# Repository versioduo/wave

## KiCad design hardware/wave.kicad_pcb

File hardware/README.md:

# wave
🔊 MIDI Wave Synthesizer with Class-D Amplifier 

## Schematic
[PDF](wave.pdf)

## Bill Of Materials
[Interactive BOM](https://html-preview.github.io/?url=https://github.com/versioduo/wave/main/hardware/wave-bom.html)

# Copying
Anyone can use this public domain work without having to seek authorisation, no one can ever own it.

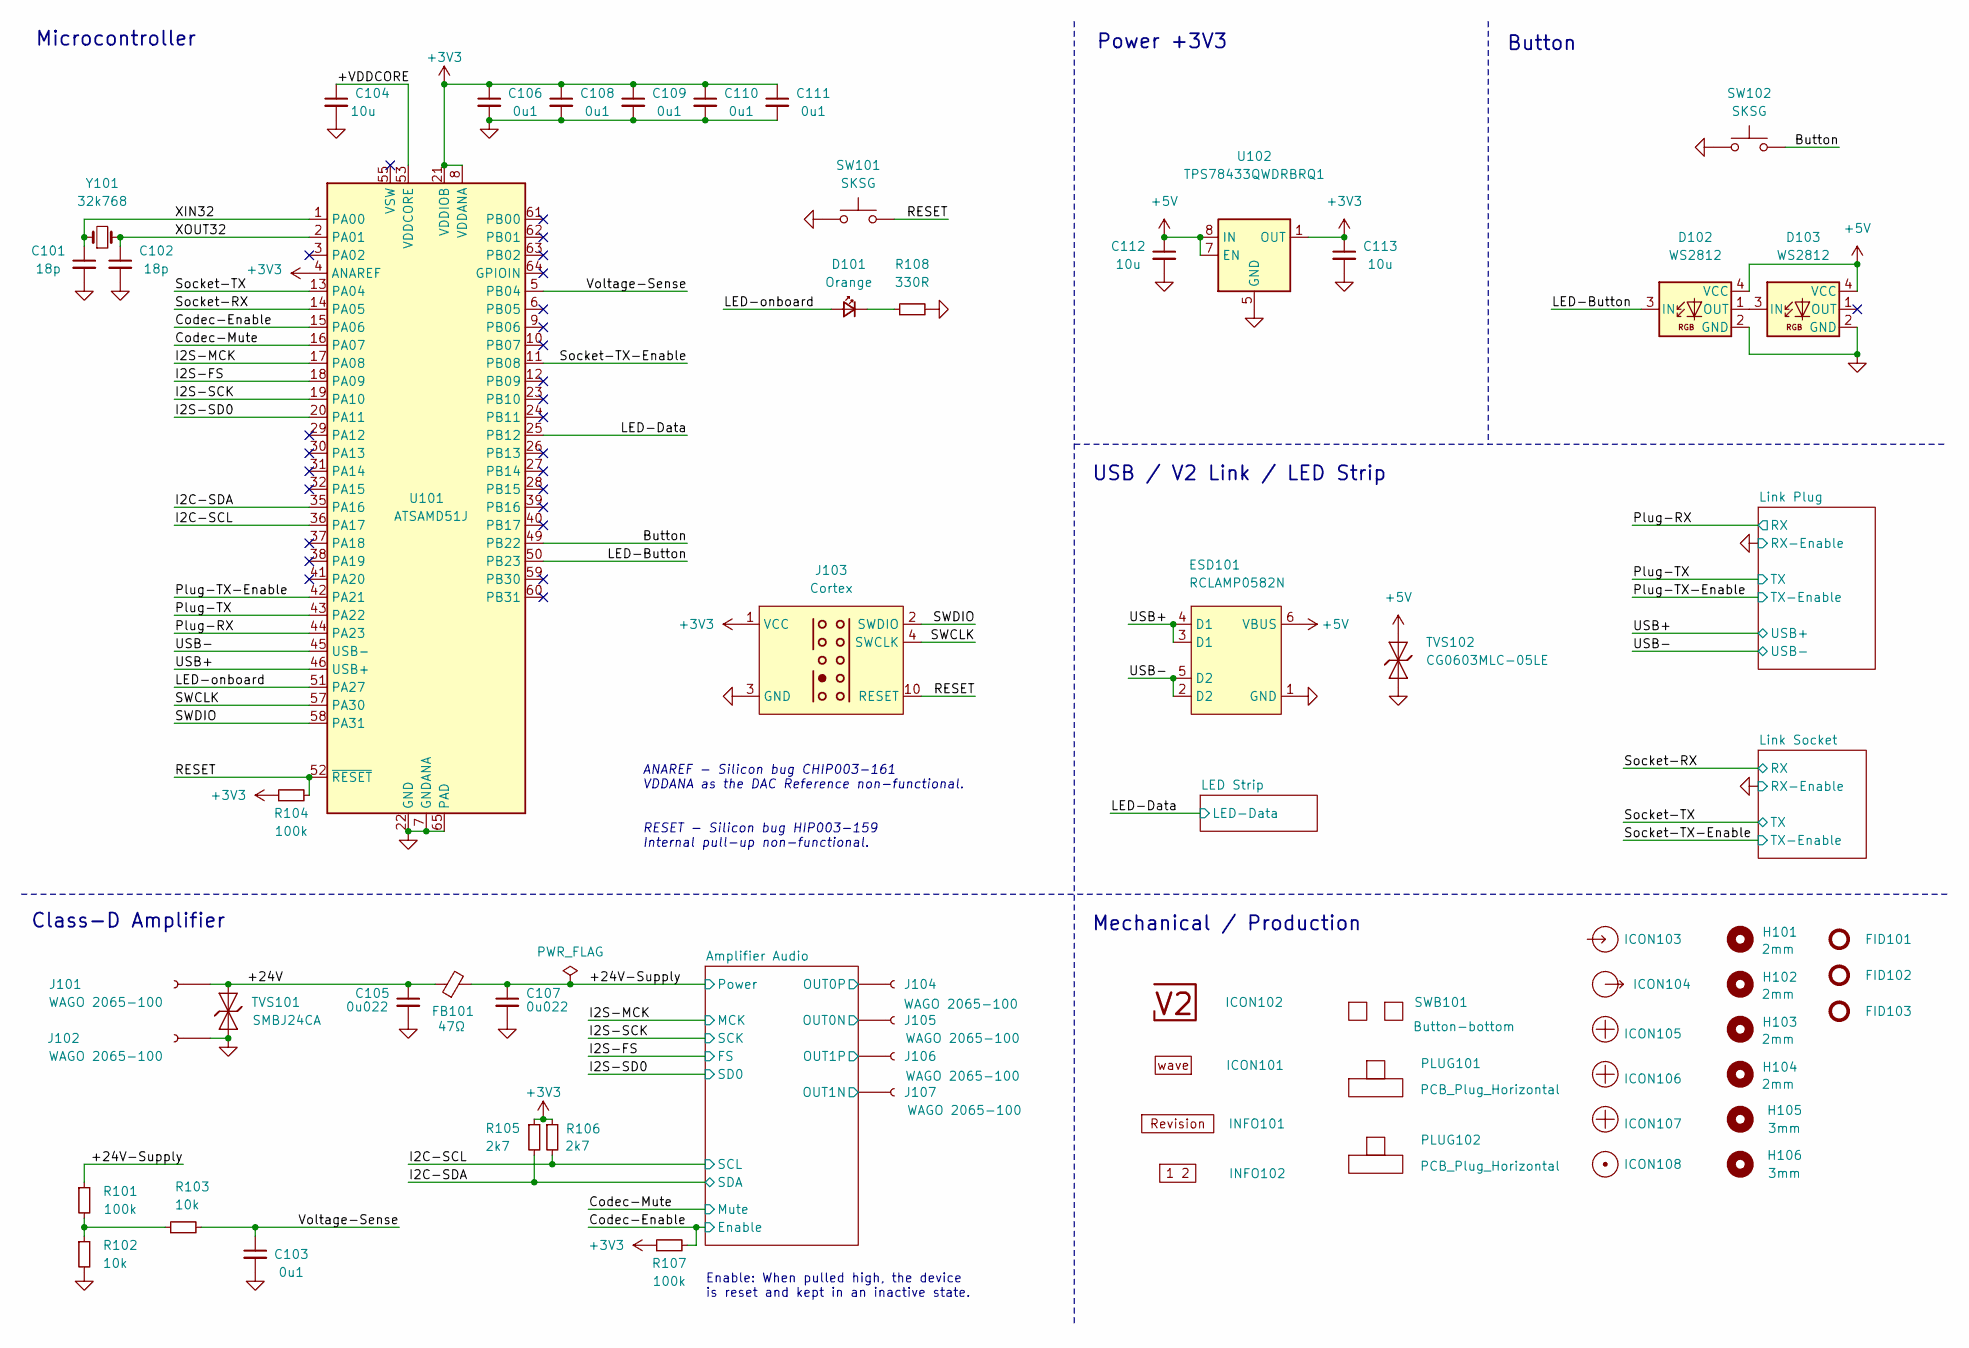
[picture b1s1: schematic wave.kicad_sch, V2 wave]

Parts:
C101, C102: 18p; C_1608; Rating 50V; Mouser 810-CGA3E2C0G1H180J
C103, C106, C108, C109, C110, C111: 0u1; C_1608; Rating 50V; Mouser 810-CGA3E2X7R1H104MA
C104: 10u; C_1608; Rating 10V; Mouser 810-C1608X6S1A106M
C105, C107: 0u022; C_1608; Rating 50V; Mouser 603-CC603KPX7R9BB223
C112, C113: 10u; C_2012; Rating 25V; Mouser 810-C2012X5R1E106K
D101: Orange; LED_1608; Rating 605nm; Mouser 755-SML-D12D1WT86
D102, D103: WS2812; WS2812-2020; Rating 15mA; LCSC C965555
ESD101: RCLAMP0582N; SLP1210N6; Rating 20kV; Mouser 947-RCLAMP0582N.TCT
FB101: 47Ω; L_3.1x5.1; Rating 5A; Mouser 623-2743019447LF
FID101, FID102, FID103: Fiducial_Paste; Fiducial_0.5mm_Mask1mm_Paste
H101, H102, H103, H104: 2mm; MountingHole_2mm
H105, H106: 3mm; MountingHole_3mm
ICON101: Board_wave; Board_wave_Small
ICON102: V2-logo; Logo_Small
ICON103: Arrow_In
ICON104: Arrow_Out
ICON105, ICON106, ICON107: Plus; Plus_Small
ICON108: Dot; Dot_Small
INFO101: Revision
INFO102: Layer_Numbers-4
J101, J102, J104, J105, J106, J107: WAGO 2065-100; 2065-100; Rating 9A
J103: Cortex
PLUG101, PLUG102: PCB_Plug_Horizontal
R101, R104, R107: 100k; R_1608; Rating 100mW; Mouser 71-CRCW0603100KFKEAC
R102, R103: 10k; R_1608; Rating 100mW; Mouser 71-CRCW060310K0FKEAC
R105, R106: 2k7; R_1608; Rating 100mW; Mouser 71-CRCW06032K70FKEAC
R108: 330R; R_1608; Rating 100mW; Mouser 71-CRCW0603330RFKEAC
SW101, SW102: SKSG; Rating 1.6N; Mouser 688-SKSGACE010
SWB101: Button-bottom; PCB_Button-bottom
TVS101: SMBJ24CA; D_SMB; Rating 24V; Mouser 652-SMBJ24CA-Q
TVS102: CG0603MLC-05LE; D_1608; Rating 5V; Mouser 652-CG0603MLC-05LE
U101: ATSAMD51J; QFN-64-1EP_9x9mm_P0.5mm_EP4.8x4.8mm_ThermalVias; Rating Cortex-M4F; Mouser 556-ATSAMD51J19AMU
U102: TPS78433QWDRBRQ1; VSON-8-1_3x3mm_P0.65_EP1.65x2.4mm; Rating 300mA; Mouser 595-TPS78433QWDRBRQ1
Y101: 32k768; Crystal_SMD_3215-2Pin_3.2x1.5mm; Rating 10ppm; Mouser 815-ABS0716632.768KT

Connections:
+3V3: C106.1, C108.1, C109.1, C110.1, C111.1, C113.1, J103.1 (VCC), R104.1, R105.1, R106.1, R107.1, U101.4 (ANAREF), U101.8 (VDDANA), U101.21 (VDDIOB), U101.34 (VDDIO), U101.48 (VDDIO), U101.56 (VDDIO), U102.1 (OUT); also elsewhere on the board
+5V: C112.1, D102.4 (VCC), D103.4 (VCC), ESD101.6 (VBUS), TVS102.2 (A), U102.7 (EN), U102.8 (IN); also elsewhere on the board
/+24V: C105.1, FB101.1, J101.1, TVS101.2 (A)
/+24V-Supply: C107.1, FB101.2, R101.1; also elsewhere on the board
/+VDDCORE: C104.1, U101.53 (VDDCORE)
/Amplifier Audio/OUT0N: J105.1; also elsewhere on the board
/Amplifier Audio/OUT0P: J104.1; also elsewhere on the board
/Amplifier Audio/OUT1N: J107.1; also elsewhere on the board
/Amplifier Audio/OUT1P: J106.1; also elsewhere on the board
/Button: SW102.2, U101.49 (PB22)
/Codec-Enable: R107.2, U101.15 (PA06); also elsewhere on the board
/Codec-Mute: U101.16 (PA07); also elsewhere on the board
/I2C-SCL: R106.2, U101.36 (PA17); also elsewhere on the board
/I2C-SDA: R105.2, U101.35 (PA16); also elsewhere on the board
/I2S-FS: U101.18 (PA09); also elsewhere on the board
/I2S-MCK: U101.17 (PA08); also elsewhere on the board
/I2S-SCK: U101.19 (PA10); also elsewhere on the board
/I2S-SD0: U101.20 (PA11); also elsewhere on the board
/LED-Button: D102.3 (IN), U101.50 (PB23)
/LED-Data: U101.25 (PB12); also elsewhere on the board
/LED-onboard: D101.2 (A), U101.51 (PA27)
/Plug-RX: U101.44 (PA23); also elsewhere on the board
/Plug-TX: U101.43 (PA22); also elsewhere on the board
/Plug-TX-Enable: U101.42 (PA21); also elsewhere on the board
/RESET: J103.10 (RESET), R104.2, SW101.2, U101.52 (~RESET)
/SWCLK: J103.4 (SWCLK), U101.57 (PA30)
/SWDIO: J103.2 (SWDIO), U101.58 (PA31)
/Socket-RX: U101.14 (PA05); also elsewhere on the board
/Socket-TX: U101.13 (PA04); also elsewhere on the board
/Socket-TX-Enable: U101.11 (PB08); also elsewhere on the board
/USB+: ESD101.3 (D1), ESD101.4 (D1), U101.46 (USB+); also elsewhere on the board
/USB-: ESD101.2 (D2), ESD101.5 (D2), U101.45 (USB-); also elsewhere on the board
/Voltage-Sense: C103.1, R103.2, U101.5 (PB04)
/XIN32: C101.1, U101.1 (PA00), Y101.1
/XOUT32: C102.1, U101.2 (PA01), Y101.2
GND: C101.2, C102.2, C103.2, C104.2, C105.2, C106.2, C107.2, C108.2, C109.2, C110.2, C111.2, C112.2, C113.2, D102.2 (GND), D103.2 (GND), ESD101.1 (GND), J102.1, J103.3 (GND), J103.5 (GND), R102.2, R108.2, SW101.1, SW102.1, TVS101.1 (K), TVS102.1 (K), U101.7 (GNDANA), U101.22 (GND), U101.33 (GND), U101.47 (GND), U101.54 (GND), U101.65 (PAD), U102.5 (GND), U102.9 (GND); also elsewhere on the board
unnamed: D101.1 (K), R108.1
unnamed: D102.1 (OUT), D103.3 (IN)
unnamed: R101.2, R102.1, R103.1

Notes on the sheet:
﻿ANAREF - Silicon bug CHIP003-161 VDDANA as the DAC Reference non-functional.
RESET - ﻿Silicon bug HIP003-159 Internal pull-up non-functional.
Button
USB / V2 Link / LED Strip
Mechanical / Production
Power +3V3
Enable: When pulled high, the device is reset and kept in an inactive state.
Microcontroller
Class-D Amplifier

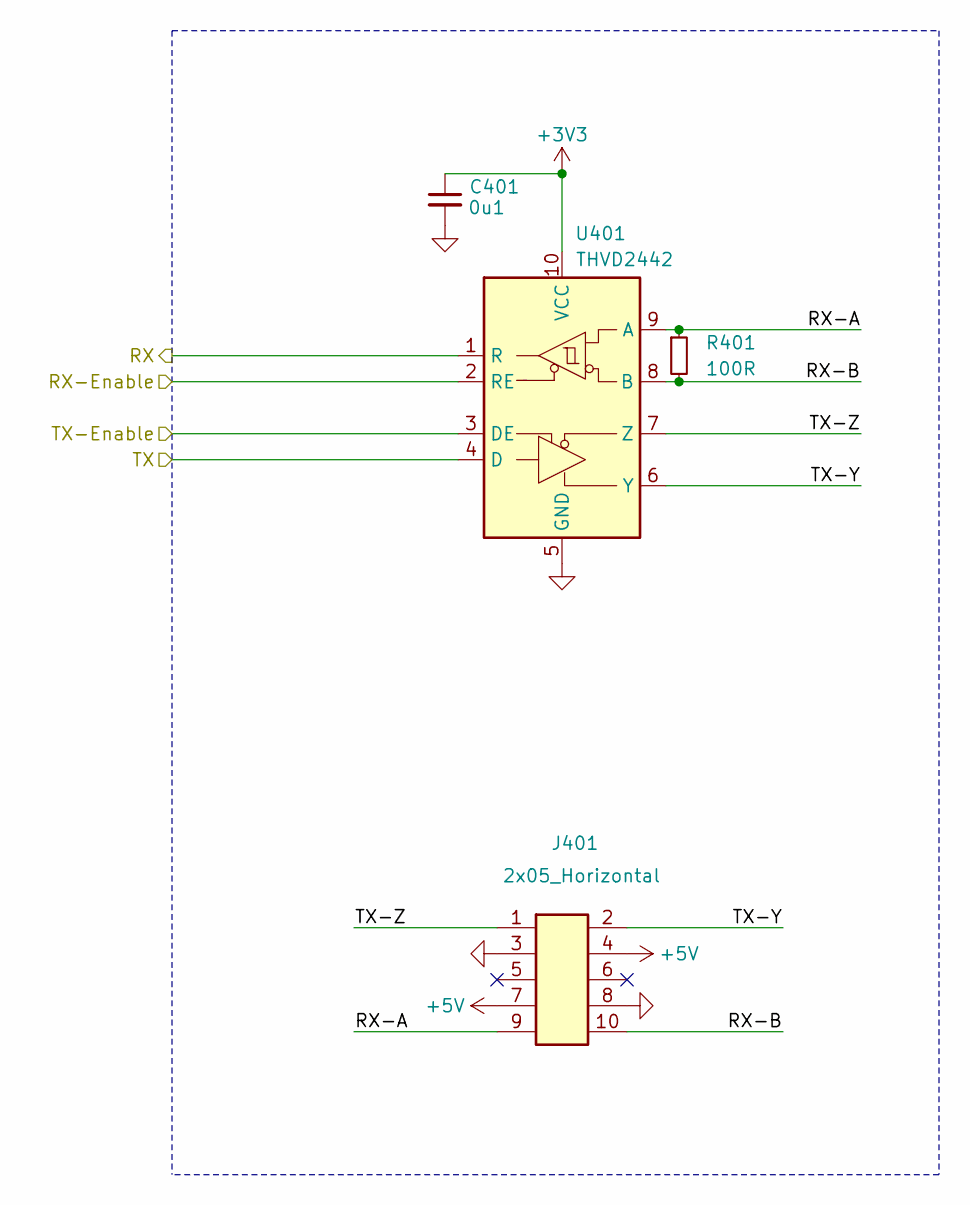
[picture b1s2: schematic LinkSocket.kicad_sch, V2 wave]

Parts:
C401: 0u1; C_1608; Rating 50V; Mouser 810-CGA3E2X7R1H104MA
J401: 2x05_Horizontal; PinHeader_2x05_P1.27mm_Horizontal; Rating 1A; Mouser 649-200211120001T4LF
R401: 100R; R_1608; Rating 330mW; Mouser 71-CRCW0603100RFKEAH
U401: THVD2442; VSON-10-4-1EP_3x3mm_P0.5mm_EP1.65x2.4mm_ThermalVias; Rating 20Mbps; Mouser 595-THVD2442DRCR

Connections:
+3V3: C401.1, U401.10 (VCC); also elsewhere on the board
+5V: J401.4, J401.7; also elsewhere on the board
/Link Socket/RX-A: J401.9, R401.1, U401.9 (A)
/Link Socket/RX-B: J401.10, R401.2, U401.8 (B)
/Link Socket/TX-Y: J401.2, U401.6 (Y)
/Link Socket/TX-Z: J401.1, U401.7 (Z)
/Socket-RX: U401.1 (R); also elsewhere on the board
/Socket-TX: U401.4 (D); also elsewhere on the board
/Socket-TX-Enable: U401.3 (DE); also elsewhere on the board
GND: C401.2, J401.3, J401.8, U401.2 (RE), U401.5 (GND), U401.11 (GND); also elsewhere on the board

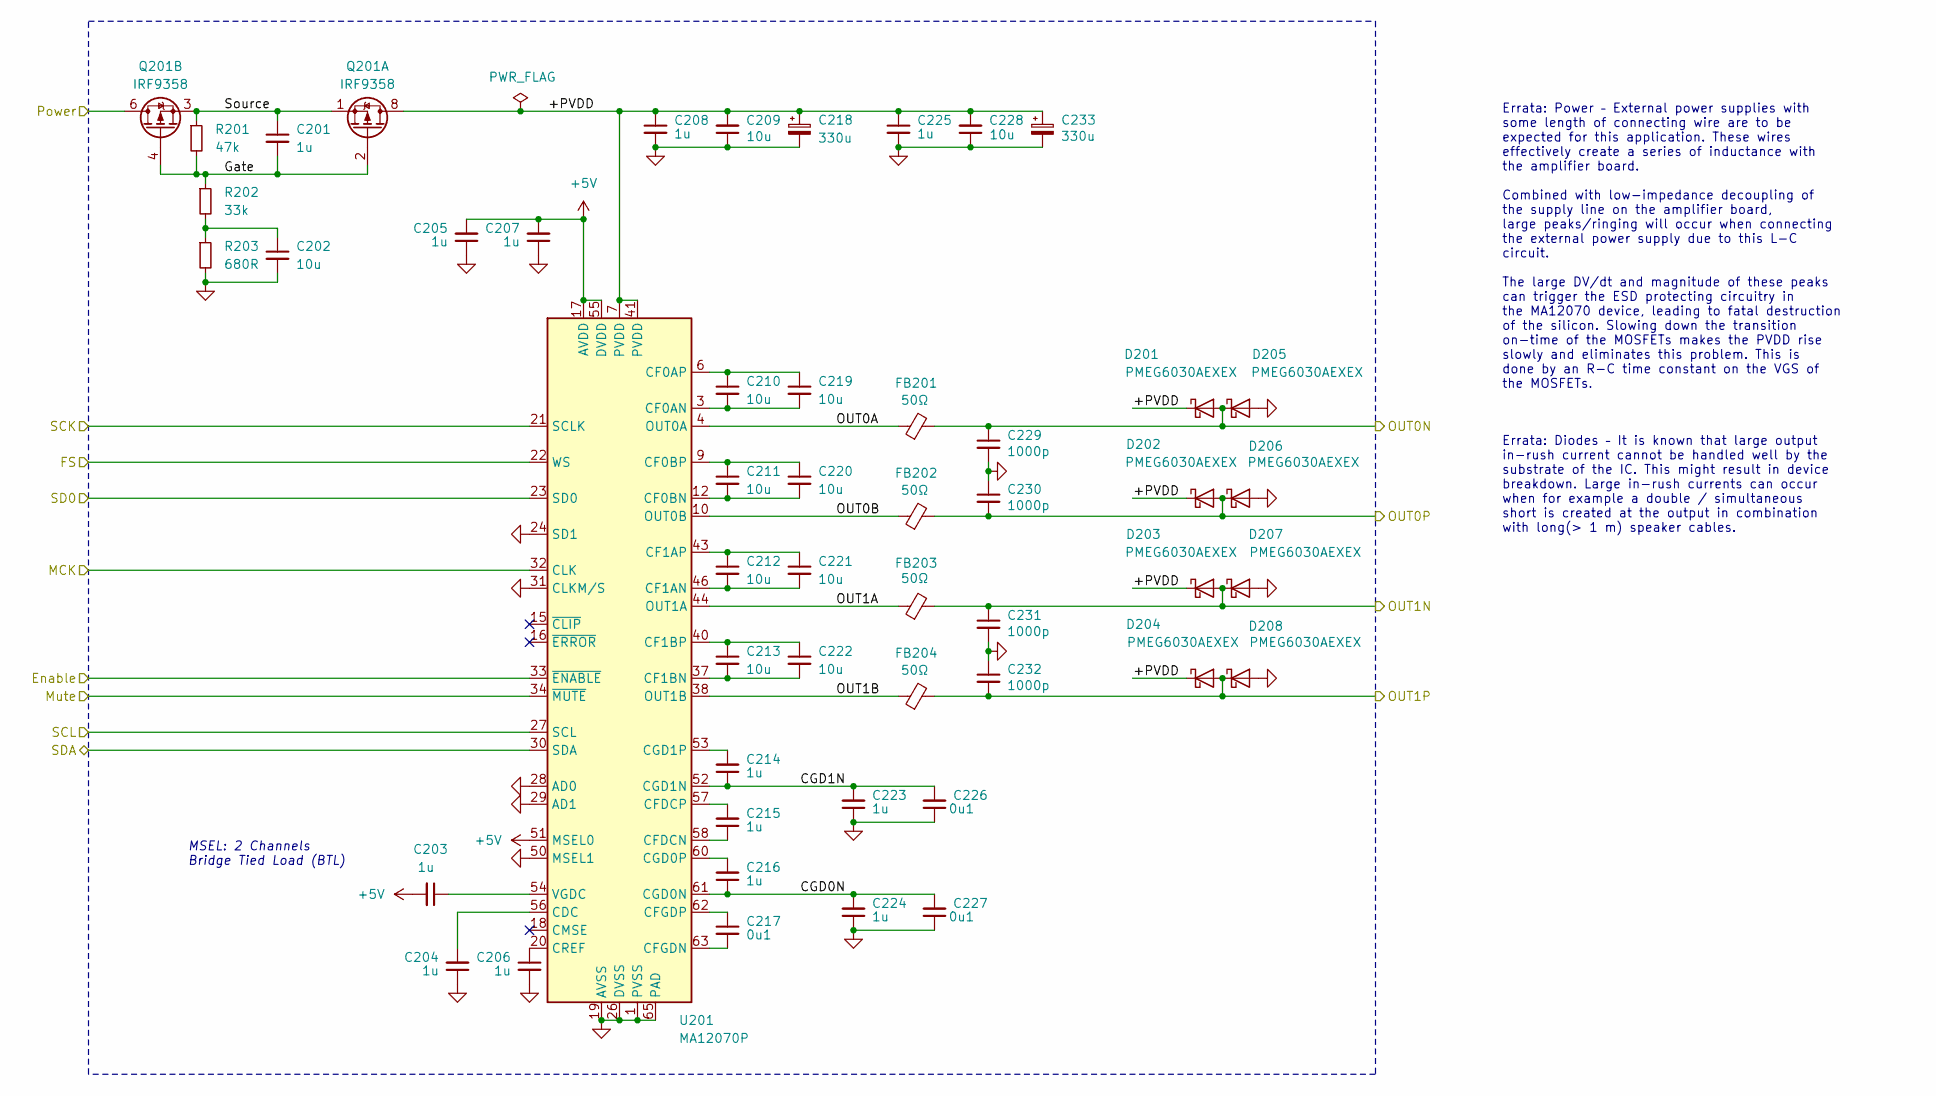
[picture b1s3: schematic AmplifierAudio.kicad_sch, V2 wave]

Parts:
C201, C203, C204, C205, C206, C207, C208, C214, C215, C216, C223, C224, C225: 1u; C_1608; Rating 50V; Mouser 810-CGA3E3X7R1H105K0
C202, C209, C210, C211, C212, C213, C219, C220, C221, C222, C228: 10u; C_1608; Rating 10V; Mouser 810-C1608X6S1A106M
C217, C226, C227: 0u1; C_1608; Rating 50V; Mouser 810-CGA3E2X7R1H104MA
C218, C233: 330u; CP_Elec_8x10; Rating 35V; Mouser 667-EEE-FT1V331GP
C229, C230, C231, C232: 1000p; C_1608; Rating 50V; Mouser 810-C1608C0G1H102J
D201, D202, D203, D204, D205, D206, D207, D208: PMEG6030AEXEX; D_SOD-123HP; Rating 60V; Mouser 771-PMEG6030AEXEX
FB201, FB202, FB203, FB204: 50Ω; L_1206; Rating 6A; Mouser 623-2512065007Y6
Q201: IRF9358; SOIC-8_3.9x4.9mm_P1.27mm; Rating 30V; Mouser 942-IRF9358TRPBF
R201: 47k; R_1608; Rating 250mW; Mouser 71-RCS060347K0FKEA
R202: 33k; R_1608; Rating 330mW; Mouser 71- 71-CRCW060333K0FKEAH
R203: 680R; R_1608; Rating 250mW; Mouser 71-RCS0603680RFKEA
U201: MA12070P; QFN-64-1EP_9x9mm_P0.5mm_EP6x6mm_ThermalVias; Rating 30W; Mouser 726-MA12070PXUMA1

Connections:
+5V: C203.2, C205.2, C207.2, U201.17 (AVDD), U201.51 (MSEL0), U201.55 (DVDD); also elsewhere on the board
/+24V-Supply: Q201.5 (D2), Q201.6 (D2); also elsewhere on the board
/Amplifier Audio/+PVDD: C208.1, C209.2, C218.1, C225.1, C228.2, C233.1, D201.1 (K), D202.1 (K), D203.1 (K), D204.1 (K), Q201.7 (D1), Q201.8 (D1), U201.7 (PVDD), U201.8 (PVDD), U201.41 (PVDD), U201.42 (PVDD)
/Amplifier Audio/CGD0N: C216.1, C224.2, C227.2, U201.61 (CGD0N)
/Amplifier Audio/CGD1N: C214.1, C223.2, C226.2, U201.52 (CGD1N)
/Amplifier Audio/Gate: C201.2, Q201.2 (G1), Q201.4 (G2), R201.2, R202.1
/Amplifier Audio/OUT0A: FB201.1, U201.4 (OUT0A), U201.5 (OUT0A)
/Amplifier Audio/OUT0B: FB202.1, U201.10 (OUT0B), U201.11 (OUT0B)
/Amplifier Audio/OUT0N: C229.1, D201.2 (A), D205.1 (K), FB201.2; also elsewhere on the board
/Amplifier Audio/OUT0P: C230.2, D202.2 (A), D206.1 (K), FB202.2; also elsewhere on the board
/Amplifier Audio/OUT1A: FB203.1, U201.44 (OUT1A), U201.45 (OUT1A)
/Amplifier Audio/OUT1B: FB204.1, U201.38 (OUT1B), U201.39 (OUT1B)
/Amplifier Audio/OUT1N: C231.1, D203.2 (A), D207.1 (K), FB203.2; also elsewhere on the board
/Amplifier Audio/OUT1P: C232.2, D204.2 (A), D208.1 (K), FB204.2; also elsewhere on the board
/Amplifier Audio/Source: C201.1, Q201.1 (S1), Q201.3 (S2), R201.1
/Codec-Enable: U201.33 (~ENABLE); also elsewhere on the board
/Codec-Mute: U201.34 (~MUTE); also elsewhere on the board
/I2C-SCL: U201.27 (SCL); also elsewhere on the board
/I2C-SDA: U201.30 (SDA); also elsewhere on the board
/I2S-FS: U201.22 (WS); also elsewhere on the board
/I2S-MCK: U201.32 (CLK); also elsewhere on the board
/I2S-SCK: U201.21 (SCLK); also elsewhere on the board
/I2S-SD0: U201.23 (SD0); also elsewhere on the board
GND: C202.2, C204.1, C205.1, C206.2, C207.1, C208.2, C209.1, C218.2, C223.1, C224.1, C225.2, C226.1, C227.1, C228.1, C229.2, C230.1, C231.2, C232.1, C233.2, D205.2 (A), D206.2 (A), D207.2 (A), D208.2 (A), R203.2, U201.1 (PVSS), U201.2 (PVSS), U201.13 (PVSS), U201.14 (PVSS), U201.19 (AVSS), U201.24 (SD1), U201.25 (AVSS), U201.26 (DVSS), U201.28 (AD0), U201.29 (AD1), U201.31 (CLKM/S), U201.35 (PVSS), U201.36 (PVSS), U201.47 (PVSS), U201.48 (PVSS), U201.50 (MSEL1), U201.59 (DVSS), U201.65 (PAD); also elsewhere on the board
unnamed: C202.1, R202.2, R203.1
unnamed: C204.2, U201.56 (CDC)
unnamed: C210.2, C219.2, U201.3 (CF0AN)
unnamed: C210.1, C219.1, U201.6 (CF0AP)
unnamed: C211.2, C220.2, U201.12 (CF0BN)
unnamed: C211.1, C220.1, U201.9 (CF0BP)
unnamed: C212.2, C221.2, U201.46 (CF1AN)
unnamed: C212.1, C221.1, U201.43 (CF1AP)
unnamed: C213.2, C222.2, U201.37 (CF1BN)
unnamed: C213.1, C222.1, U201.40 (CF1BP)
unnamed: C215.1, U201.58 (CFDCN)
unnamed: C215.2, U201.57 (CFDCP)
unnamed: C217.2, U201.63 (CFGDN)
unnamed: C217.1, U201.62 (CFGDP)
unnamed: C216.2, U201.60 (CGD0P)
unnamed: C214.2, U201.53 (CGD1P)
unnamed: C206.1, U201.20 (CREF)
unnamed: C203.1, U201.54 (VGDC)

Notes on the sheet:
Errata: Diodes – It is known that large output in-rush current cannot be handled well by the substrate of the IC. This might result in device breakdown. Large in-rush currents can occur when for example a double / simultaneous short is created at the output in combination with long(> 1 m) speaker c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
MSEL: 2 Channels Bridge Tied Load (BTL)
Errata: Power – External power supplies with some length of connecting wire are to be expected for this application. These wires effectively create a series of inductance with the amplifier board. Combined with low-impedance decoupling of the supply line on the amplifier board, large peaks/ringing 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

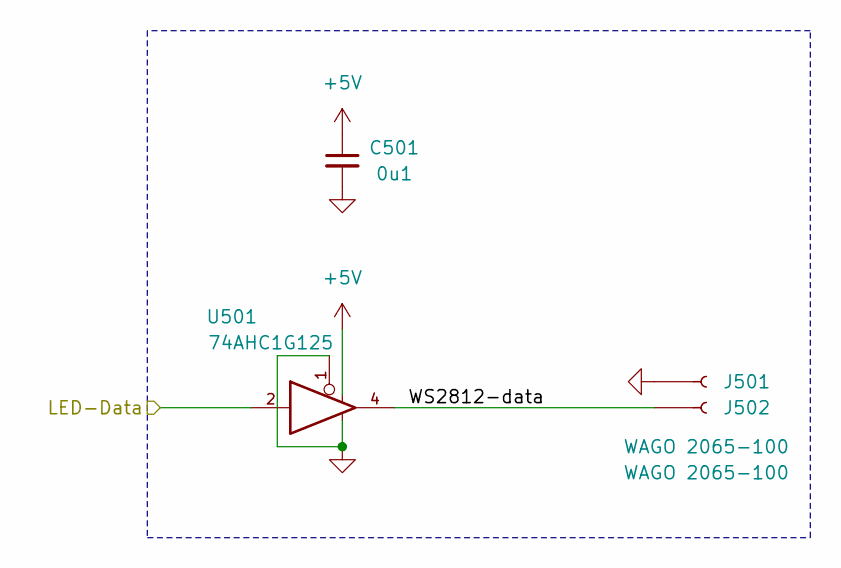
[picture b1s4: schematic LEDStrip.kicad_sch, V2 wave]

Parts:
C501: 0u1; C_1608; Rating 50V; Mouser 810-CGA3E2X7R1H104MA
J501, J502: WAGO 2065-100; 2065-100; Rating 9A
U501: 74AHC1G125; SOT-23-5; Rating 8mA; Mouser 595-SN74AHC1G125DBVR

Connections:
+5V: C501.1, U501.5; also elsewhere on the board
/LED Strip/WS2812-data: J502.1, U501.4
/LED-Data: U501.2; also elsewhere on the board
GND: C501.2, J501.1, U501.1, U501.3; also elsewhere on the board

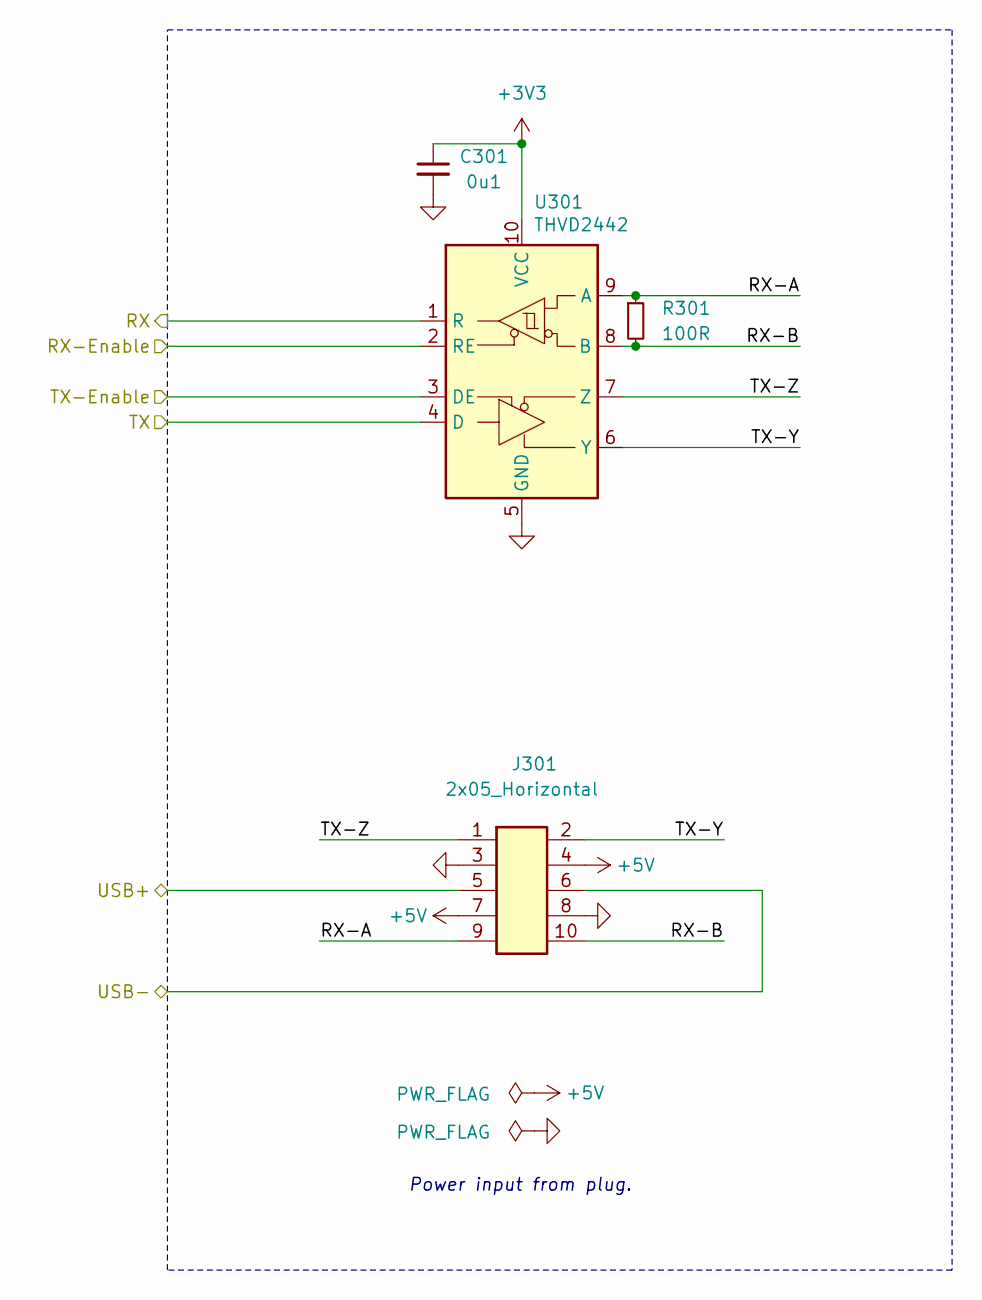
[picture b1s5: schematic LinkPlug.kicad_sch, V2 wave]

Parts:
C301: 0u1; C_1608; Rating 50V; Mouser 810-CGA3E2X7R1H104MA
J301: 2x05_Horizontal; PinHeader_2x05_P1.27mm_Horizontal; Rating 1A; Mouser 649-200211120001T4LF
R301: 100R; R_1608; Rating 330mW; Mouser 71-CRCW0603100RFKEAH
U301: THVD2442; VSON-10-4-1EP_3x3mm_P0.5mm_EP1.65x2.4mm_ThermalVias; Rating 20Mbps; Mouser 595-THVD2442DRCR

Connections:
+3V3: C301.1, U301.10 (VCC); also elsewhere on the board
+5V: J301.4, J301.7; also elsewhere on the board
/Link Plug/RX-A: J301.9, R301.1, U301.9 (A)
/Link Plug/RX-B: J301.10, R301.2, U301.8 (B)
/Link Plug/TX-Y: J301.2, U301.6 (Y)
/Link Plug/TX-Z: J301.1, U301.7 (Z)
/Plug-RX: U301.1 (R); also elsewhere on the board
/Plug-TX: U301.4 (D); also elsewhere on the board
/Plug-TX-Enable: U301.3 (DE); also elsewhere on the board
/USB+: J301.5; also elsewhere on the board
/USB-: J301.6; also elsewhere on the board
GND: C301.2, J301.3, J301.8, U301.2 (RE), U301.5 (GND), U301.11 (GND); also elsewhere on the board

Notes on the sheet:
Power input from plug.

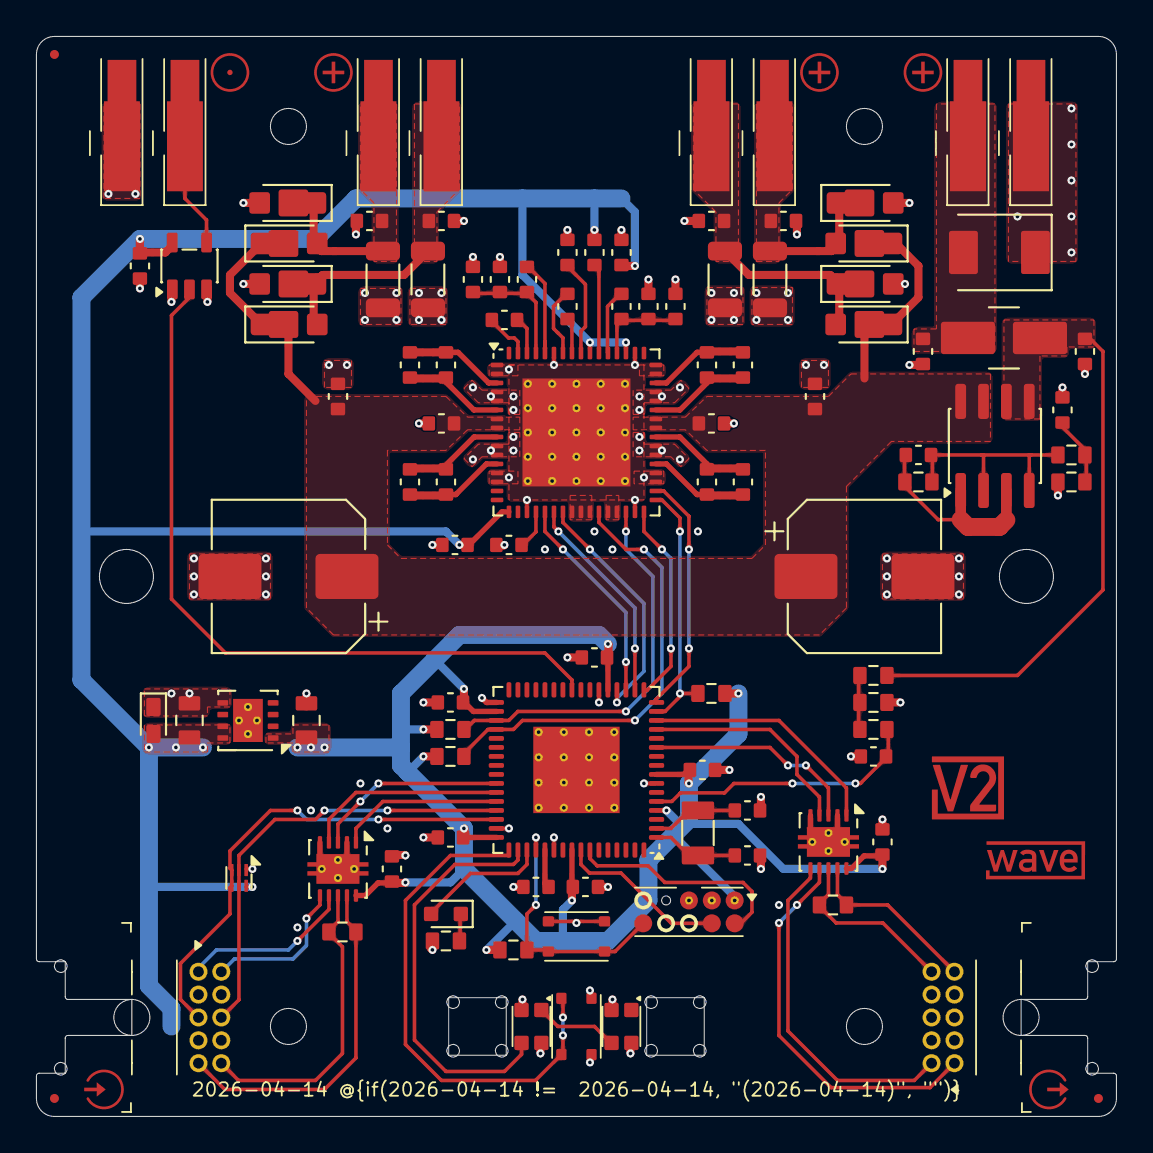
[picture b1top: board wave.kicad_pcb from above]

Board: 4 copper layers, 60.0 x 60.0 mm, 124 parts (0 on the bottom side), 75 nets.

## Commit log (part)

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2023-08-27 Import
2024-01-21 ArduinoJson 7
2025-12-29 Colour
2026-02-13 Replace Order_Number
2026-02-15 Update Library
2026-02-24 Refresh
2026-03-14 Update ESD suppressor
2026-05-11 Good Bye Imperial
2026-06-21 Update MIDI API
2026-06-23 Update V2MIDI API
